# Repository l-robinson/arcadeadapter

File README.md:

arcadeadapter
=============

PS3 arcade adapter

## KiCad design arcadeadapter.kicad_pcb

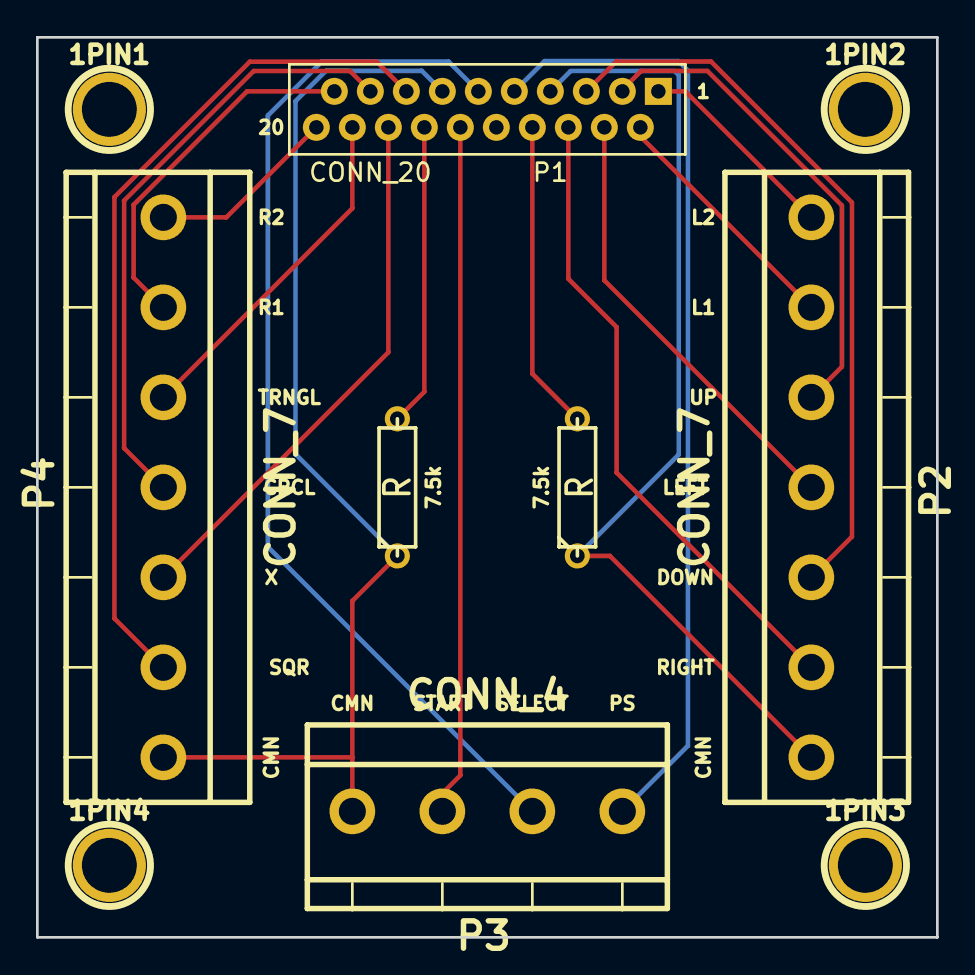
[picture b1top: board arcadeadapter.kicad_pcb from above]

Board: 2 copper layers, 50.0 x 50.0 mm, 10 parts (0 on the bottom side), 19 nets.

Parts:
1PIN1, 1PIN2, 1PIN3, 1PIN4: P***; 1pin
P1: CONN_20; 52030-2029
P2, P4: CONN_7; PCBT7
P3: CONN_4; PCBT4
R1, R2: R; R3

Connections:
unnamed: P1.12, P3.3
unnamed: P1.11, P3.2
unnamed: P1.9, P3.1
unnamed: P1.8, R2.2
unnamed: P1.7, P2.7, R2.1
unnamed: P1.6, P2.6
unnamed: P1.5, P2.5
unnamed: P1.4, P2.4
unnamed: P1.3, P2.3
unnamed: P1.20, P4.1
unnamed: P1.15, P4.6
unnamed: P1.16, P4.5
unnamed: P1.17, P4.4
unnamed: P1.18, P4.3
unnamed: P1.19, P4.2
unnamed: P1.14, R1.2
unnamed: P1.13, P3.4, P4.7, R1.1
unnamed: P1.2, P2.2
unnamed: P1.1, P2.1

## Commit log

2014-06-30 initial checkin
2014-07-12 Schematic tidy up
    Moved some overlapping wires around to make things clearer
2014-07-12 Added images
